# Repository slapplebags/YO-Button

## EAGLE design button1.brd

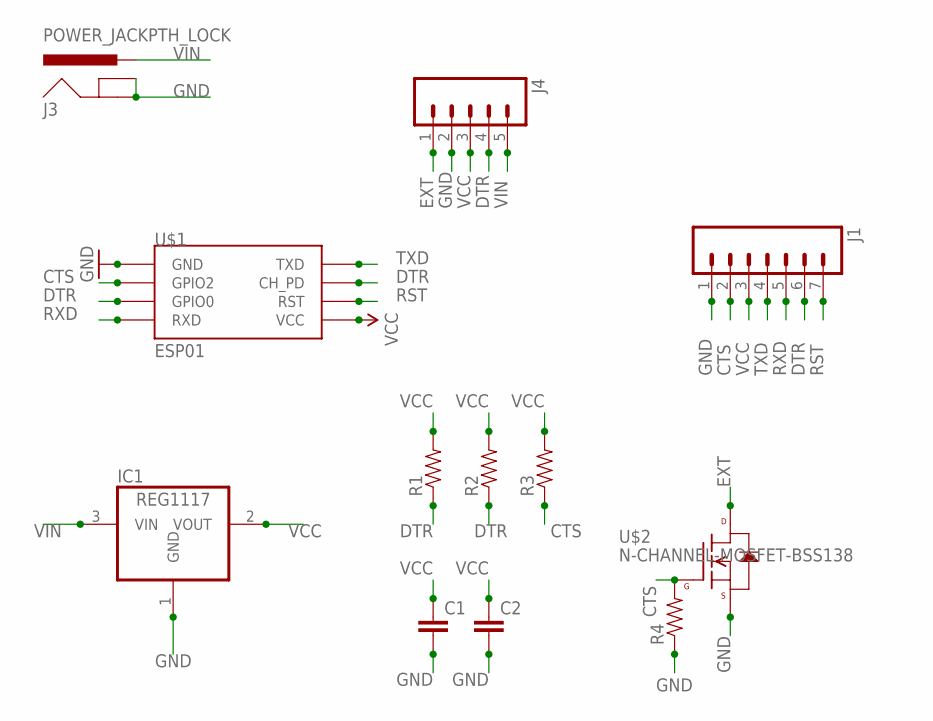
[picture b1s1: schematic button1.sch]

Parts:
C1, C2: CAP0603-CAP; 0603-CAP
IC1: REG1117; SOT223
J1: M07LOCK_LONGPADS; 1X07_LOCK_LONGPADS
J3: POWER_JACKPTH_LOCK; POWER_JACK_PTH_LOCK
J4: M05LOCK_LONGPADS; 1X05_LOCK_LONGPADS
R1, R2, R3, R4: RESISTOR0603; 0603-RES
U$1: ESP01
U$2: N-CHANNEL-MOSFET-BSS138; SOT23-3

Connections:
CTS: J1.2, R3.1, R4.2, U$1.GPIO2, U$2.1 (G)
DTR: J1.6, J4.4, R1.1, R2.1, U$1.CH_PD, U$1.GPIO0
EXT: J4.1, U$2.3 (D)
GND: C1.2, C2.2, IC1.1 (GND), J1.1, J3.GND, J3.GNDBREAK, J4.2, R4.1, U$1.GND, U$2.2 (S)
RST: J1.7, U$1.RST
RXD: J1.5, U$1.RX (RXD)
TXD: J1.4, U$1.TX (TXD)
VCC: C1.1, C2.1, IC1.2 (VOUT), J1.3, J4.3, R1.2, R2.2, R3.2, U$1.VCC
VIN: IC1.3 (VIN), J3.PWR, J4.5

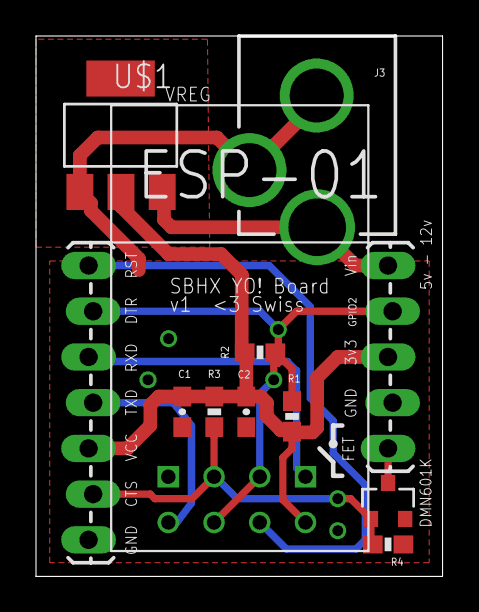
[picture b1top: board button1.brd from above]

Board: 2 copper layers, 22.6 x 30.0 mm, 12 parts (0 on the bottom side), 9 nets.

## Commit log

2017-02-05 YO! Button v1
    improved YO! button with integrated barrel jack and N Channel MOSFET

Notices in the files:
parts and their libraries:
SparkFun-Connectors: Licensing: Creative Commons ShareAlike 4.0 International - https://creativecommons.org/licenses/by-sa/4.0
